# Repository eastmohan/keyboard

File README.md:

# keyboard

This is a 64 key custom keyboard, slightly wider than a typical 60% keyboard. It uses an 8x8 key matrix, hence the 3 extra keys not typically included in a 60% keyboard. Those keys will be mapped to media controls in firmware. The project uses the Raspberry Pi Pico 2 microcontroller.

For assembly, snap the switches into the holes and place the diodes, paying close attention to orientation. Also, solder pin headers to the Raspberry Pi Pico 2 and solder those in the PCB. Snap in the stabilizers and add the keycaps. Then, put the microcontroller in boot mode with circuitpython and add the firmware.

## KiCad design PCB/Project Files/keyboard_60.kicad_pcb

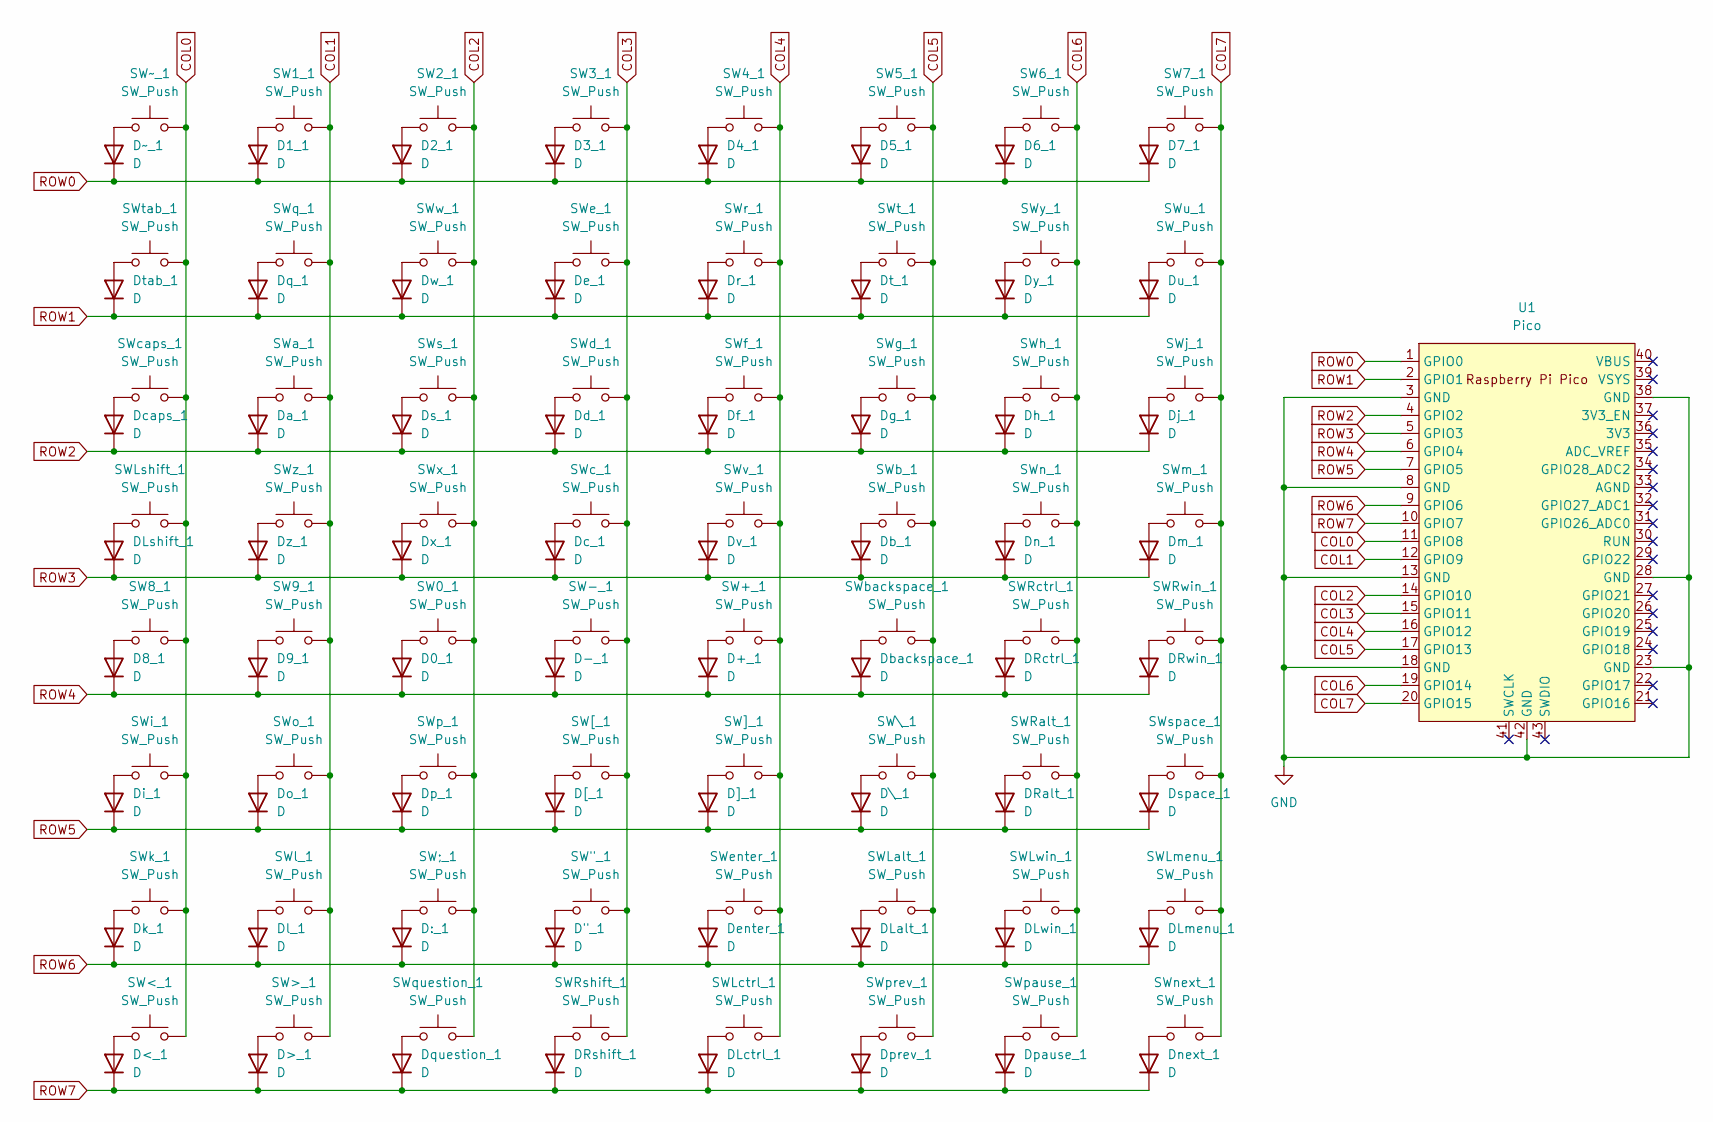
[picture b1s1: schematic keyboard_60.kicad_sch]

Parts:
D0_1, D1_1, D2_1, D3_1, D4_1, D5_1, D6_1, D7_1, D8_1, D9_1: D; D_DO-35_SOD27_P7.62mm_Horizontal
D"_1: D; D_DO-35_SOD27_P7.62mm_Horizontal
D+_1: D; D_DO-35_SOD27_P7.62mm_Horizontal
D-_1: D; D_DO-35_SOD27_P7.62mm_Horizontal
D:_1: D; D_DO-35_SOD27_P7.62mm_Horizontal
D<_1: D; D_DO-35_SOD27_P7.62mm_Horizontal
D>_1: D; D_DO-35_SOD27_P7.62mm_Horizontal
DLalt_1: D; D_DO-35_SOD27_P7.62mm_Horizontal
DLctrl_1: D; D_DO-35_SOD27_P7.62mm_Horizontal
DLmenu_1: D; D_DO-35_SOD27_P7.62mm_Horizontal
DLshift_1: D; D_DO-35_SOD27_P7.62mm_Horizontal
DLwin_1: D; D_DO-35_SOD27_P7.62mm_Horizontal
DRalt_1: D; D_DO-35_SOD27_P7.62mm_Horizontal
DRctrl_1: D; D_DO-35_SOD27_P7.62mm_Horizontal
DRshift_1: D; D_DO-35_SOD27_P7.62mm_Horizontal
DRwin_1: D; D_DO-35_SOD27_P7.62mm_Horizontal
D[_1: D; D_DO-35_SOD27_P7.62mm_Horizontal
D\_1: D; D_DO-35_SOD27_P7.62mm_Horizontal
D]_1: D; D_DO-35_SOD27_P7.62mm_Horizontal
Da_1: D; D_DO-35_SOD27_P7.62mm_Horizontal
Db_1: D; D_DO-35_SOD27_P7.62mm_Horizontal
Dbackspace_1: D; D_DO-35_SOD27_P7.62mm_Horizontal
Dc_1: D; D_DO-35_SOD27_P7.62mm_Horizontal
Dcaps_1: D; D_DO-35_SOD27_P7.62mm_Horizontal
Dd_1: D; D_DO-35_SOD27_P7.62mm_Horizontal
De_1: D; D_DO-35_SOD27_P7.62mm_Horizontal
Denter_1: D; D_DO-35_SOD27_P7.62mm_Horizontal
Df_1: D; D_DO-35_SOD27_P7.62mm_Horizontal
Dg_1: D; D_DO-35_SOD27_P7.62mm_Horizontal
Dh_1: D; D_DO-35_SOD27_P7.62mm_Horizontal
Di_1: D; D_DO-35_SOD27_P7.62mm_Horizontal
Dj_1: D; D_DO-35_SOD27_P7.62mm_Horizontal
Dk_1: D; D_DO-35_SOD27_P7.62mm_Horizontal
Dl_1: D; D_DO-35_SOD27_P7.62mm_Horizontal
Dm_1: D; D_DO-35_SOD27_P7.62mm_Horizontal
Dn_1: D; D_DO-35_SOD27_P7.62mm_Horizontal
Dnext_1: D; D_DO-35_SOD27_P7.62mm_Horizontal
Do_1: D; D_DO-35_SOD27_P7.62mm_Horizontal
Dp_1: D; D_DO-35_SOD27_P7.62mm_Horizontal
Dpause_1: D; D_DO-35_SOD27_P7.62mm_Horizontal
Dprev_1: D; D_DO-35_SOD27_P7.62mm_Horizontal
Dq_1: D; D_DO-35_SOD27_P7.62mm_Horizontal
Dquestion_1: D; D_DO-35_SOD27_P7.62mm_Horizontal
Dr_1: D; D_DO-35_SOD27_P7.62mm_Horizontal
Ds_1: D; D_DO-35_SOD27_P7.62mm_Horizontal
Dspace_1: D; D_DO-35_SOD27_P7.62mm_Horizontal
Dt_1: D; D_DO-35_SOD27_P7.62mm_Horizontal
Dtab_1: D; D_DO-35_SOD27_P7.62mm_Horizontal
Du_1: D; D_DO-35_SOD27_P7.62mm_Horizontal
Dv_1: D; D_DO-35_SOD27_P7.62mm_Horizontal
Dw_1: D; D_DO-35_SOD27_P7.62mm_Horizontal
Dx_1: D; D_DO-35_SOD27_P7.62mm_Horizontal
Dy_1: D; D_DO-35_SOD27_P7.62mm_Horizontal
Dz_1: D; D_DO-35_SOD27_P7.62mm_Horizontal
D~_1: D; D_DO-35_SOD27_P7.62mm_Horizontal
SW0_1, SW1_1, SW2_1, SW3_1, SW4_1, SW5_1, SW6_1, SW7_1, SW8_1, SW9_1: SW_Push; SW_Cherry_MX_1.00u_PCB
SW"_1: SW_Push; SW_Cherry_MX_1.00u_PCB
SW+_1: SW_Push; SW_Cherry_MX_1.00u_PCB
SW-_1: SW_Push; SW_Cherry_MX_1.00u_PCB
SW;_1: SW_Push; SW_Cherry_MX_1.00u_PCB
SW<_1: SW_Push; SW_Cherry_MX_1.00u_PCB
SW>_1: SW_Push; SW_Cherry_MX_1.00u_PCB
SWLalt_1: SW_Push; SW_Cherry_MX_1.25u_PCB
SWLctrl_1: SW_Push; SW_Cherry_MX_1.25u_PCB
SWLmenu_1: SW_Push; SW_Cherry_MX_1.25u_PCB
SWLshift_1: SW_Push; SW_Cherry_MX_2.75u_PCB
SWLwin_1: SW_Push; SW_Cherry_MX_1.25u_PCB
SWRalt_1: SW_Push; SW_Cherry_MX_1.25u_PCB
SWRctrl_1: SW_Push; SW_Cherry_MX_1.25u_PCB
SWRshift_1: SW_Push; SW_Cherry_MX_2.25u_PCB
SWRwin_1: SW_Push; SW_Cherry_MX_1.25u_PCB
SW[_1: SW_Push; SW_Cherry_MX_1.00u_PCB
SW\_1: SW_Push; SW_Cherry_MX_1.00u_PCB
SW]_1: SW_Push; SW_Cherry_MX_1.00u_PCB
SWa_1: SW_Push; SW_Cherry_MX_1.00u_PCB
SWb_1: SW_Push; SW_Cherry_MX_1.00u_PCB
SWbackspace_1: SW_Push; SW_Cherry_MX_2.00u_PCB
SWc_1: SW_Push; SW_Cherry_MX_1.00u_PCB
SWcaps_1: SW_Push; SW_Cherry_MX_1.75u_PCB
SWd_1: SW_Push; SW_Cherry_MX_1.00u_PCB
SWe_1: SW_Push; SW_Cherry_MX_1.00u_PCB
SWenter_1: SW_Push; SW_Cherry_MX_2.25u_PCB
SWf_1: SW_Push; SW_Cherry_MX_1.00u_PCB
SWg_1: SW_Push; SW_Cherry_MX_1.00u_PCB
SWh_1: SW_Push; SW_Cherry_MX_1.00u_PCB
SWi_1: SW_Push; SW_Cherry_MX_1.00u_PCB
SWj_1: SW_Push; SW_Cherry_MX_1.00u_PCB
SWk_1: SW_Push; SW_Cherry_MX_1.00u_PCB
SWl_1: SW_Push; SW_Cherry_MX_1.00u_PCB
SWm_1: SW_Push; SW_Cherry_MX_1.00u_PCB
SWn_1: SW_Push; SW_Cherry_MX_1.00u_PCB
SWnext_1: SW_Push; SW_Cherry_MX_1.00u_PCB
SWo_1: SW_Push; SW_Cherry_MX_1.00u_PCB
SWp_1: SW_Push; SW_Cherry_MX_1.00u_PCB
SWpause_1: SW_Push; SW_Cherry_MX_1.00u_PCB
SWprev_1: SW_Push; SW_Cherry_MX_1.00u_PCB
SWq_1: SW_Push; SW_Cherry_MX_1.00u_PCB
SWquestion_1: SW_Push; SW_Cherry_MX_1.00u_PCB
SWr_1: SW_Push; SW_Cherry_MX_1.00u_PCB
SWs_1: SW_Push; SW_Cherry_MX_1.00u_PCB
SWspace_1: SW_Push; SW_Cherry_MX_6.25u_PCB
SWt_1: SW_Push; SW_Cherry_MX_1.00u_PCB
SWtab_1: SW_Push; SW_Cherry_MX_1.50u_PCB
SWu_1: SW_Push; SW_Cherry_MX_1.00u_PCB
SWv_1: SW_Push; SW_Cherry_MX_1.00u_PCB
SWw_1: SW_Push; SW_Cherry_MX_1.00u_PCB
SWx_1: SW_Push; SW_Cherry_MX_1.00u_PCB
SWy_1: SW_Push; SW_Cherry_MX_1.00u_PCB
SWz_1: SW_Push; SW_Cherry_MX_1.00u_PCB
SW~_1: SW_Push; SW_Cherry_MX_1.00u_PCB
U1: Pico; RPi_Pico_SMD_TH

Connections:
COL0: SW8_1.2, SW<_1.2, SWLshift_1.2, SWcaps_1.2, SWi_1.2, SWk_1.2, SWtab_1.2, SW~_1.2, U1.11 (GPIO8)
COL1: SW1_1.2, SW9_1.2, SW>_1.2, SWa_1.2, SWl_1.2, SWo_1.2, SWq_1.2, SWz_1.2, U1.12 (GPIO9)
COL2: SW0_1.2, SW2_1.2, SW;_1.2, SWp_1.2, SWquestion_1.2, SWs_1.2, SWw_1.2, SWx_1.2, U1.14 (GPIO10)
COL3: SW3_1.2, SW"_1.2, SW-_1.2, SWRshift_1.2, SW[_1.2, SWc_1.2, SWd_1.2, SWe_1.2, U1.15 (GPIO11)
COL4: SW4_1.2, SW+_1.2, SWLctrl_1.2, SW]_1.2, SWenter_1.2, SWf_1.2, SWr_1.2, SWv_1.2, U1.16 (GPIO12)
COL5: SW5_1.2, SWLalt_1.2, SW\_1.2, SWb_1.2, SWbackspace_1.2, SWg_1.2, SWprev_1.2, SWt_1.2, U1.17 (GPIO13)
COL6: SW6_1.2, SWLwin_1.2, SWRalt_1.2, SWRctrl_1.2, SWh_1.2, SWn_1.2, SWpause_1.2, SWy_1.2, U1.19 (GPIO14)
COL7: SW7_1.2, SWLmenu_1.2, SWRwin_1.2, SWj_1.2, SWm_1.2, SWnext_1.2, SWspace_1.2, SWu_1.2, U1.20 (GPIO15)
GND: U1.3 (GND), U1.8 (GND), U1.13 (GND), U1.18 (GND), U1.23 (GND), U1.28 (GND), U1.38 (GND), U1.42 (GND)
unnamed: D0_1.2 (A), SW0_1.1
unnamed: D1_1.2 (A), SW1_1.1
unnamed: D2_1.2 (A), SW2_1.1
unnamed: D3_1.2 (A), SW3_1.1
unnamed: D4_1.2 (A), SW4_1.1
unnamed: D5_1.2 (A), SW5_1.1
unnamed: D6_1.2 (A), SW6_1.1
unnamed: D7_1.2 (A), SW7_1.1
unnamed: D8_1.2 (A), SW8_1.1
unnamed: D9_1.2 (A), SW9_1.1
unnamed: D"_1.2 (A), SW"_1.1
unnamed: D+_1.2 (A), SW+_1.1
unnamed: D-_1.2 (A), SW-_1.1
unnamed: D:_1.2 (A), SW;_1.1
unnamed: D<_1.2 (A), SW<_1.1
unnamed: D>_1.2 (A), SW>_1.1
unnamed: DLalt_1.2 (A), SWLalt_1.1
unnamed: DLctrl_1.2 (A), SWLctrl_1.1
unnamed: DLmenu_1.2 (A), SWLmenu_1.1
unnamed: DLshift_1.2 (A), SWLshift_1.1
unnamed: DLwin_1.2 (A), SWLwin_1.1
unnamed: DRalt_1.2 (A), SWRalt_1.1
unnamed: DRctrl_1.2 (A), SWRctrl_1.1
unnamed: DRshift_1.2 (A), SWRshift_1.1
unnamed: DRwin_1.2 (A), SWRwin_1.1
unnamed: D[_1.2 (A), SW[_1.1
unnamed: D\_1.2 (A), SW\_1.1
unnamed: D]_1.2 (A), SW]_1.1
unnamed: Da_1.2 (A), SWa_1.1
unnamed: Db_1.2 (A), SWb_1.1
unnamed: Dbackspace_1.2 (A), SWbackspace_1.1
unnamed: Dc_1.2 (A), SWc_1.1
unnamed: Dcaps_1.2 (A), SWcaps_1.1
unnamed: Dd_1.2 (A), SWd_1.1
unnamed: De_1.2 (A), SWe_1.1
unnamed: Denter_1.2 (A), SWenter_1.1
unnamed: Df_1.2 (A), SWf_1.1
unnamed: Dg_1.2 (A), SWg_1.1
unnamed: Dh_1.2 (A), SWh_1.1
unnamed: Di_1.2 (A), SWi_1.1
unnamed: Dj_1.2 (A), SWj_1.1
unnamed: Dk_1.2 (A), SWk_1.1
unnamed: Dl_1.2 (A), SWl_1.1
unnamed: Dm_1.2 (A), SWm_1.1
unnamed: Dn_1.2 (A), SWn_1.1
unnamed: Dnext_1.2 (A), SWnext_1.1
unnamed: Do_1.2 (A), SWo_1.1
unnamed: Dp_1.2 (A), SWp_1.1
unnamed: Dpause_1.2 (A), SWpause_1.1
unnamed: Dprev_1.2 (A), SWprev_1.1
unnamed: Dq_1.2 (A), SWq_1.1
unnamed: Dquestion_1.2 (A), SWquestion_1.1
unnamed: Dr_1.2 (A), SWr_1.1
unnamed: Ds_1.2 (A), SWs_1.1
unnamed: Dspace_1.2 (A), SWspace_1.1
unnamed: Dt_1.2 (A), SWt_1.1
unnamed: Dtab_1.2 (A), SWtab_1.1
unnamed: Du_1.2 (A), SWu_1.1
unnamed: Dv_1.2 (A), SWv_1.1
unnamed: Dw_1.2 (A), SWw_1.1
unnamed: Dx_1.2 (A), SWx_1.1
unnamed: Dy_1.2 (A), SWy_1.1
unnamed: Dz_1.2 (A), SWz_1.1
unnamed: D~_1.2 (A), SW~_1.1
ROW0: D1_1.1 (K), D2_1.1 (K), D3_1.1 (K), D4_1.1 (K), D5_1.1 (K), D6_1.1 (K), D7_1.1 (K), D~_1.1 (K), U1.1 (GPIO0)
ROW1: De_1.1 (K), Dq_1.1 (K), Dr_1.1 (K), Dt_1.1 (K), Dtab_1.1 (K), Du_1.1 (K), Dw_1.1 (K), Dy_1.1 (K), U1.2 (GPIO1)
ROW2: Da_1.1 (K), Dcaps_1.1 (K), Dd_1.1 (K), Df_1.1 (K), Dg_1.1 (K), Dh_1.1 (K), Dj_1.1 (K), Ds_1.1 (K), U1.4 (GPIO2)
ROW3: DLshift_1.1 (K), Db_1.1 (K), Dc_1.1 (K), Dm_1.1 (K), Dn_1.1 (K), Dv_1.1 (K), Dx_1.1 (K), Dz_1.1 (K), U1.5 (GPIO3)
ROW4: D0_1.1 (K), D8_1.1 (K), D9_1.1 (K), D+_1.1 (K), D-_1.1 (K), DRctrl_1.1 (K), DRwin_1.1 (K), Dbackspace_1.1 (K), U1.6 (GPIO4)
ROW5: DRalt_1.1 (K), D[_1.1 (K), D\_1.1 (K), D]_1.1 (K), Di_1.1 (K), Do_1.1 (K), Dp_1.1 (K), Dspace_1.1 (K), U1.7 (GPIO5)
ROW6: D"_1.1 (K), D:_1.1 (K), DLalt_1.1 (K), DLmenu_1.1 (K), DLwin_1.1 (K), Denter_1.1 (K), Dk_1.1 (K), Dl_1.1 (K), U1.9 (GPIO6)
ROW7: D<_1.1 (K), D>_1.1 (K), DLctrl_1.1 (K), DRshift_1.1 (K), Dnext_1.1 (K), Dpause_1.1 (K), Dprev_1.1 (K), Dquestion_1.1 (K), U1.10 (GPIO7)

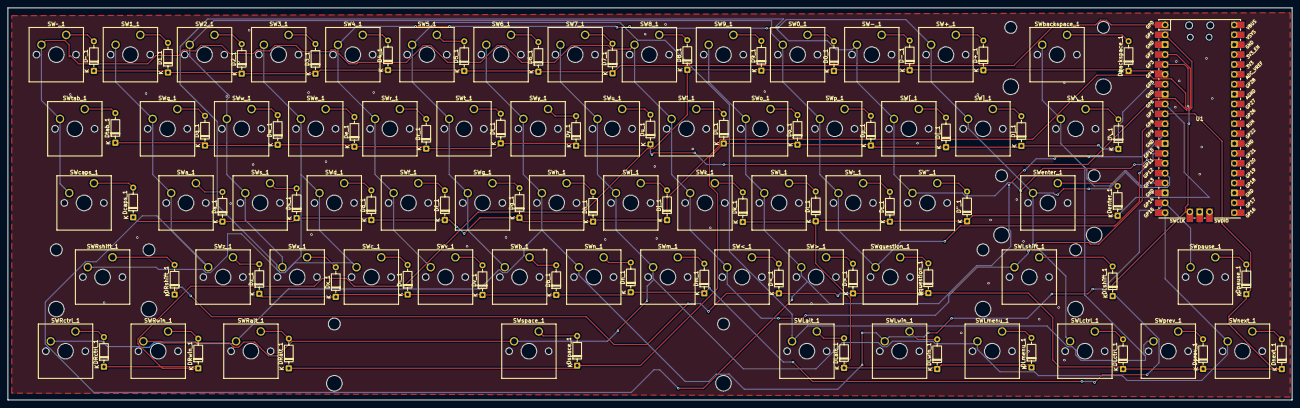
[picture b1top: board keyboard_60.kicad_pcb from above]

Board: 2 copper layers, 330.0 x 100.8 mm, 129 parts (0 on the bottom side), 81 nets.
